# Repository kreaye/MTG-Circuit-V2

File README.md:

# MTG-Circuit-V2
Electrical circuit and PCB design

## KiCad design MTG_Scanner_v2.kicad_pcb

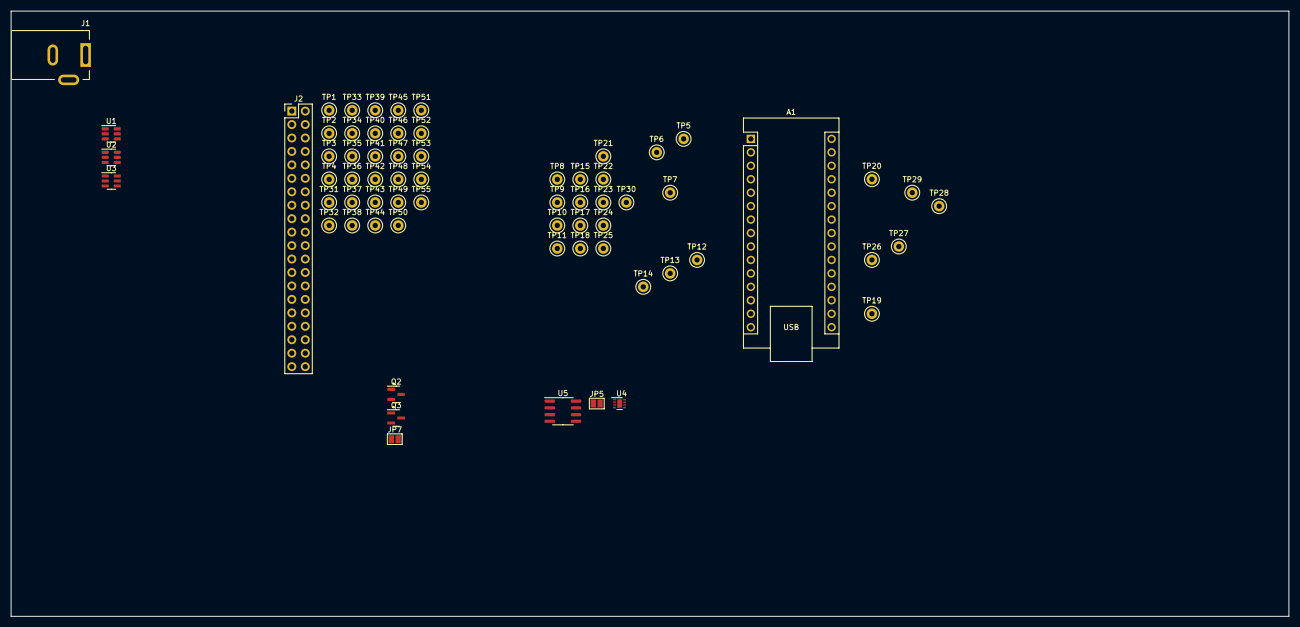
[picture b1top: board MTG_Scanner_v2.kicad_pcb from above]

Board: 2 copper layers, 241.3 x 114.3 mm, 67 parts (0 on the bottom side), 62 nets, no tracks yet.

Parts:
A1: Arduino_Nano_Every; Arduino_Nano
J1: Barrel_Jack_MountingPin; BarrelJack_Kycon_KLDX-0202-xC_Horizontal
J2: Raspberry_Pi_2_3; PinHeader_2x20_P2.54mm_Vertical
JP5, JP7: SolderJumper_2_Open; SolderJumper-2_P1.3mm_Open_Pad1.0x1.5mm
Q2, Q3: BSS138; SOT-23
TP1, TP2, TP3, TP4, TP5, TP6, TP7, TP8, TP9, TP10, TP11, TP12, TP13, TP14, TP15, TP16, TP17, TP18, TP19, TP20, TP21, TP22, TP23, TP24, TP25, TP26, TP27, TP28, TP29, TP30, TP31, TP32, TP33, TP34, TP35, TP36, TP37, TP38, TP39, TP40, TP41, TP42, TP43, TP44, TP45, TP46, TP47, TP48, TP49, TP50, TP51, TP52, TP53, TP54, TP55: TestPoint; TestPoint_Keystone_5000-5004_Miniature
U1, U2: AOZ1280CI; SOT-23-6
U3: AOZ1282CI; SOT-23-6
U4: DRV8838; WSON-8-1EP_2x2mm_P0.5mm_EP0.9x1.6mm
U5: ACS724xLCTR-05AB; SOIC-8_3.9x4.9mm_P1.27mm

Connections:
+3.3V: JP5.2 (B), JP7.2 (B), Q2.1 (G), Q3.1 (G)
+5V: U4.8 (VCC), U5.8 (VCC)
+6V: A1.30 (VIN), U1.5 (VIN), U2.5 (VIN), U3.4 (EN), U3.5 (VIN), U4.1 (VM)
/Arduino & ESP32/I2C_SCL_A: A1.24 (SCL/A5), TP22.1
/Arduino & ESP32/I2C_SDA_A: A1.23 (SDA/A4), TP21.1
/Arduino & ESP32/LED_Switch: A1.5 (D2), TP7.1
/Arduino & ESP32/Motor_C: A1.20 (A1), TP25.1, U5.7 (VIOUT)
/Arduino & ESP32/Motor_Dir: A1.7 (D4), TP9.1, U4.6 (PH)
/Arduino & ESP32/Motor_En: A1.10 (D7), TP12.1, U4.7 (~SLEEP)
/Arduino & ESP32/Motor_PWM: A1.8 (D5), TP10.1, U4.5 (EN)
/Arduino & ESP32/RX_A: A1.2 (RX1), TP6.1
/Arduino & ESP32/Servo1_PWM: A1.9 (D6), TP11.1
/Arduino & ESP32/Servo2_PWM: A1.12 (D9), TP14.1
/Arduino & ESP32/Servo3_PWM: A1.13 (D10), TP15.1
/Arduino & ESP32/TX_A: A1.1 (TX1), TP5.1
/I2C_SCL_RPI: J2.5 (SCL/GPIO3), Q3.2 (S), TP4.1
/I2C_SDA_RPI: J2.3 (SDA/GPIO2), Q2.2 (S), TP3.1
GND: A1.4 (GND), A1.29 (GND), J1.2, J2.6 (GND), J2.9 (GND), J2.14 (GND), J2.20 (GND), J2.25 (GND), J2.30 (GND), J2.34 (GND), J2.39 (GND), U1.2 (GND), U2.2 (GND), U3.2 (GND), U4.4 (GND), U4.9 (GND), U5.5 (GND)
unnamed: A1.17 (3V3), TP19.1
unnamed: A1.27 (+5V), TP20.1
unnamed: A1.19 (A0), TP24.1
unnamed: A1.21 (A2), TP26.1
unnamed: A1.22 (A3), TP27.1
unnamed: A1.25 (A6), TP28.1
unnamed: A1.26 (A7), TP29.1
unnamed: A1.6 (D3), TP8.1
unnamed: A1.11 (D8), TP13.1
unnamed: A1.15 (MISO), TP17.1
unnamed: A1.14 (MOSI), TP16.1
unnamed: A1.16 (SCK), TP18.1
unnamed: A1.3 (~RESET), A1.28 (~RESET), TP23.1
unnamed: J2.7 (GCLK0/GPIO4), TP32.1
unnamed: J2.29 (GCLK1/GPIO5), TP33.1
unnamed: J2.31 (GCLK2/GPIO6), TP34.1
unnamed: J2.8 (GPIO14/TXD), TP42.1
unnamed: J2.10 (GPIO15/RXD), TP43.1
unnamed: J2.36 (GPIO16), TP44.1
unnamed: J2.11 (GPIO17), TP45.1
unnamed: J2.12 (GPIO18/PWM0), TP46.1
unnamed: J2.35 (GPIO19/MISO1), TP47.1
unnamed: J2.38 (GPIO20/MOSI1), TP48.1
unnamed: J2.40 (GPIO21/SCLK1), TP49.1
unnamed: J2.15 (GPIO22), TP50.1
unnamed: J2.16 (GPIO23), TP51.1
unnamed: J2.18 (GPIO24), TP52.1
unnamed: J2.22 (GPIO25), TP53.1
unnamed: J2.37 (GPIO26), TP54.1
unnamed: J2.13 (GPIO27), TP55.1
unnamed: J2.28 (ID_SC/GPIO1), TP31.1
unnamed: J2.27 (ID_SD/GPIO0), TP1.1
unnamed: J2.21 (MISO0/GPIO9), TP37.1
unnamed: J2.19 (MOSI0/GPIO10), TP38.1
unnamed: J2.32 (PWM0/GPIO12), TP40.1
unnamed: J2.33 (PWM1/GPIO13), TP41.1
unnamed: J2.23 (SCLK0/GPIO11), TP39.1
unnamed: J2.24 (~CE0/GPIO8), TP36.1
unnamed: J2.26 (~CE1/GPIO7), TP35.1
unnamed: JP5.1 (A), TP30.1
unnamed: J2.2 (5V), J2.4 (5V)
unnamed: J2.1 (3V3), J2.17 (3V3), JP7.1 (A), TP2.1
unnamed: U5.1 (IP+), U5.2 (IP+)
unnamed: U4.3 (OUT2), U5.3 (IP-), U5.4 (IP-)
